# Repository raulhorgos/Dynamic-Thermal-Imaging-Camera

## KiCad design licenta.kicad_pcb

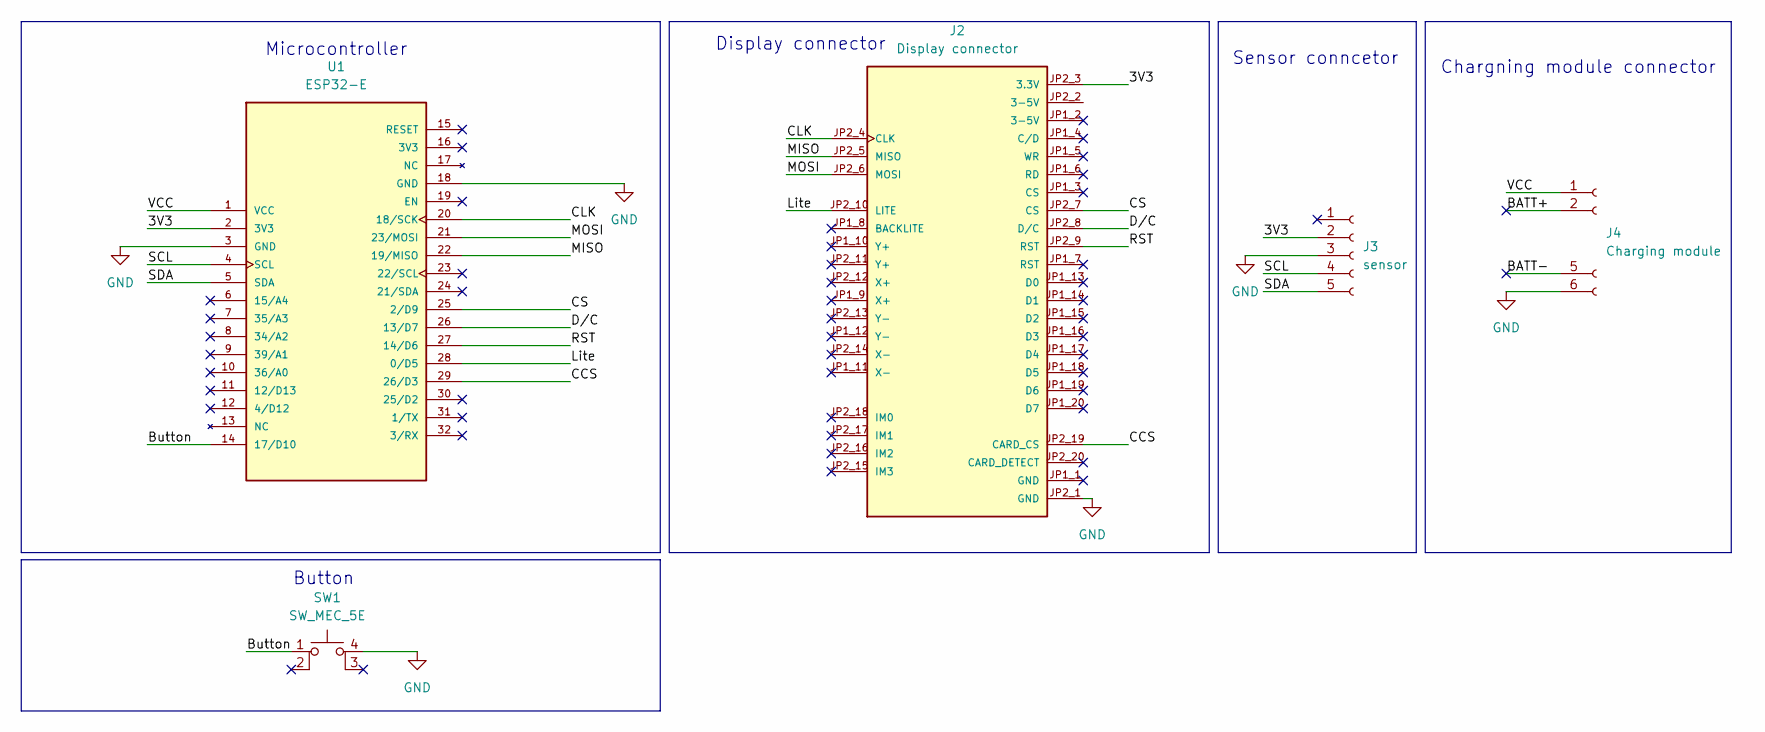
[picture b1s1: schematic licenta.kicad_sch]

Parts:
J2: Display connector; J2; PARTREV 2025-02-10
J3: sensor; Sensor
J4: Charging module; Charging
SW1: SW_MEC_5E; SW_PUSH-12mm
U1: ESP32-E; J1

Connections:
/3V3: J2.JP2_3 (3.3V), J3.2 (3Vo), U1.2 (3V3)
/BATT+: J4.2 (B+)
/BATT-: J4.5 (B-)
/Button: SW1.1, U1.14 (17/D10)
/CCS: J2.JP2_19 (CARD_CS), U1.29 (26/D3)
/CLK: J2.JP2_4 (CLK), U1.20 (18/SCK)
/CS: J2.JP2_7 (CS), U1.25 (2/D9)
/D/C: J2.JP2_8 (D/C), U1.26 (13/D7)
/Lite: J2.JP2_10 (LITE), U1.28 (0/D5)
/MISO: J2.JP2_5 (MISO), U1.22 (19/MISO)
/MOSI: J2.JP2_6 (MOSI), U1.21 (23/MOSI)
/RST: J2.JP2_9 (RST), U1.27 (14/D6)
/SCL: J3.4 (SCL), U1.4 (SCL)
/SDA: J3.5 (SDA), U1.5 (SDA)
/VCC: J4.1 (OUT+), U1.1 (VCC)
GND: J2.JP2_1 (GND), J3.3 (GND), J4.6 (OUT-), SW1.4 (A), U1.3 (GND), U1.18 (GND)

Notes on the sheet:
Sensor conncetor
Microcontroller
Button
Chargning module connector
Display connector

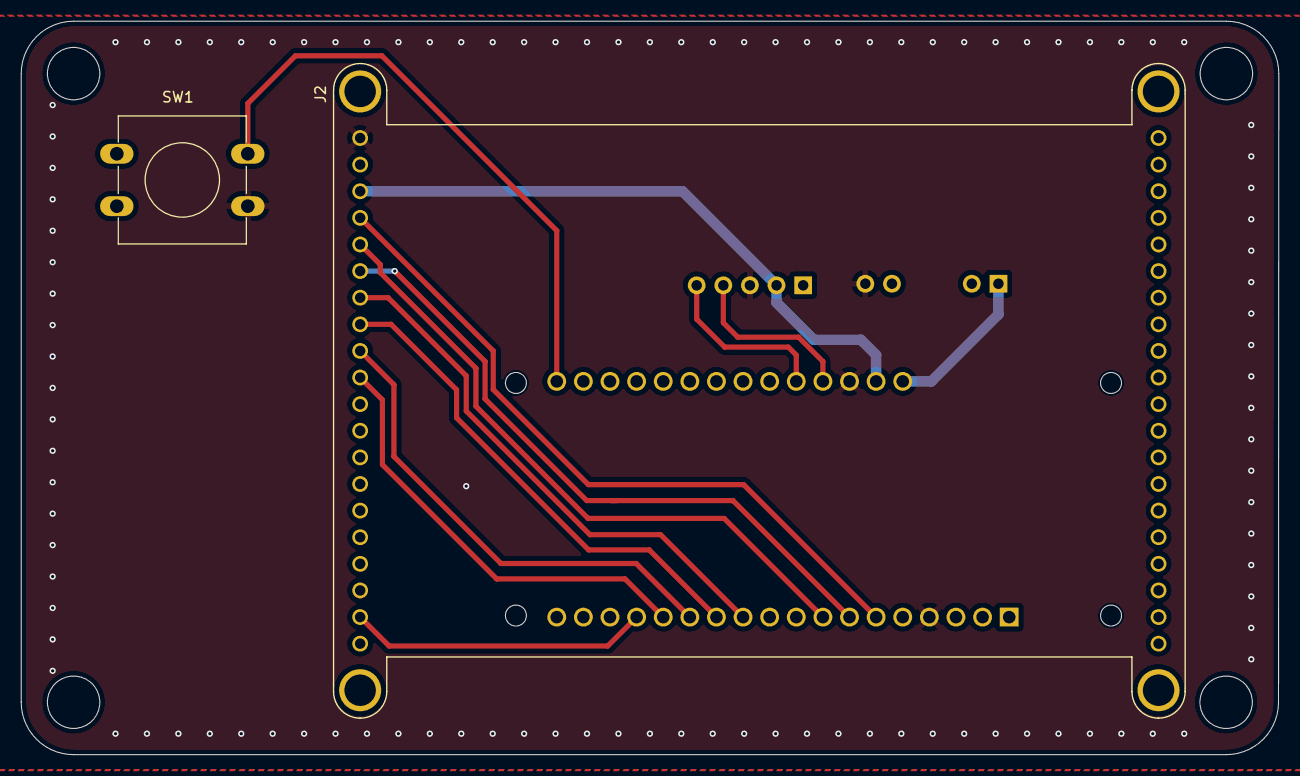
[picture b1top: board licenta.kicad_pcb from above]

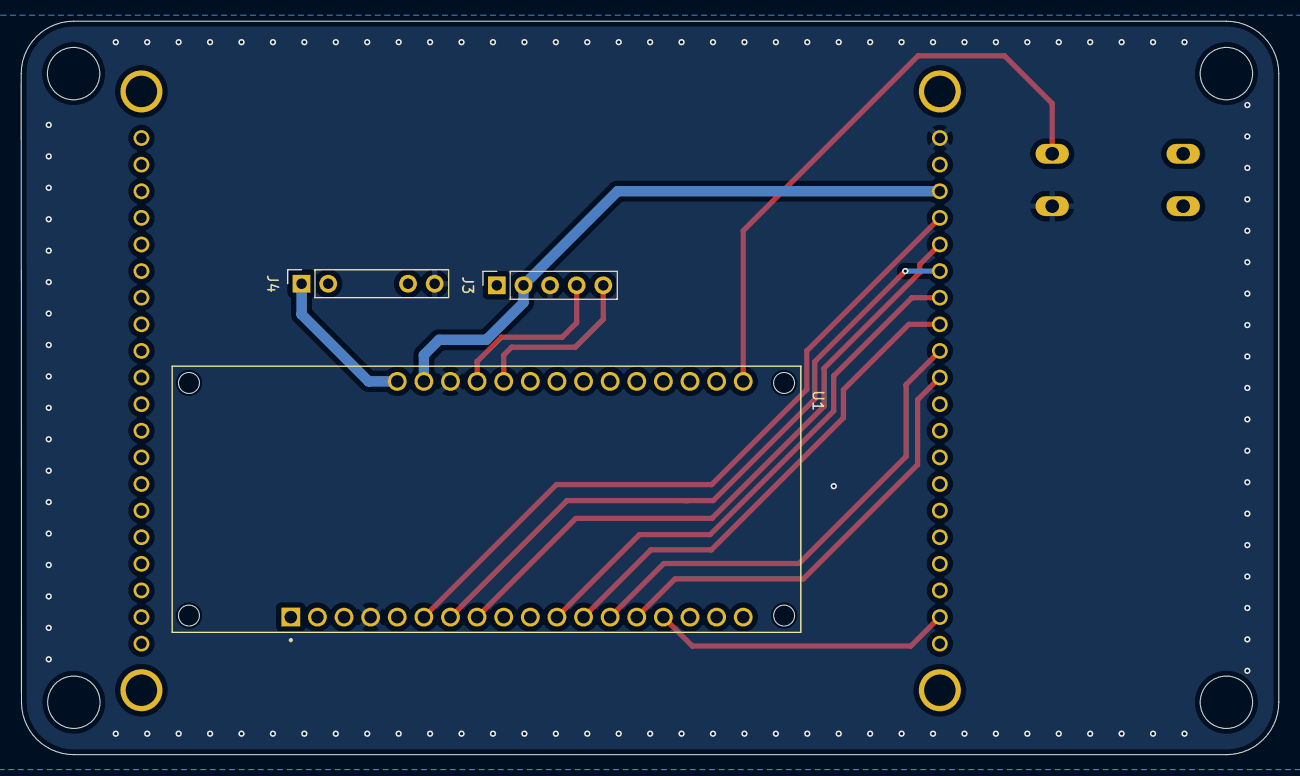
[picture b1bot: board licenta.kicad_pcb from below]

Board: 2 copper layers, 120.0 x 70.0 mm, 5 parts (3 on the bottom side), 14 nets.
